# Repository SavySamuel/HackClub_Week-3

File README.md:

# HackClub Week 3: MIDI Keypad

A custom-designed MIDI input device featuring tactile mechanical switches, analog sliders, rotary encoders, and capacitive touch pads.

---

## Overview

This project is a custom MIDI controller built around the waveshare ESP32-S3-ZERO microcontroller. It integrates multiple types of user input: push buttons, sliders, a rotary encoder, and capacitive touch channels which allows for real-time control over music production.

---

## Schematics & Layout

### Schematic
The complete schematic details the wiring for the ESP32-S3-ZERO, rotary encoders (`SW4`), slide potentiometers (`RV1`, `RV2`), mechanical push switches (`SW1`–`SW3`), and capacitive touch headers.

### PCB Layout
The custom 2-layer printed circuit board layout designed in KiCad, routing signals across the front (`F.Cu`) and back (`B.Cu`) copper layers along with some cool art I created a while ago.

### 3D Model
A 3D render preview showcasing the physical layout and placement of components on the hardware.

---

## Features & Hardware Components

- **Microcontroller:** ESP32-S3-ZERO
- **Inputs:**
	- 3x Mechanical Push Switches (`SW1`–`SW3`)
	- 2x Slide Potentiometers / Sliders (`RV1`, `RV2`)
	- 1x Rotary Encoder with Push Switch (`SW4`)
	- Capacitive Touch Button Header (`J1`)

---

> The [Journal](./JOURNAL.md) file details my experience this week

---

## Onshape Case for storing the MIDI Keypad

[Onshape Link](https://cad.onshape.com/documents/9c3e4e1773f598a6c621c8e7/w/239b4c5f4313af9012ed1455/e/c954f826d795d710e863c1da)

> Just a box to store the midi without damaging it. Made it with my MIDI's dimension in sight

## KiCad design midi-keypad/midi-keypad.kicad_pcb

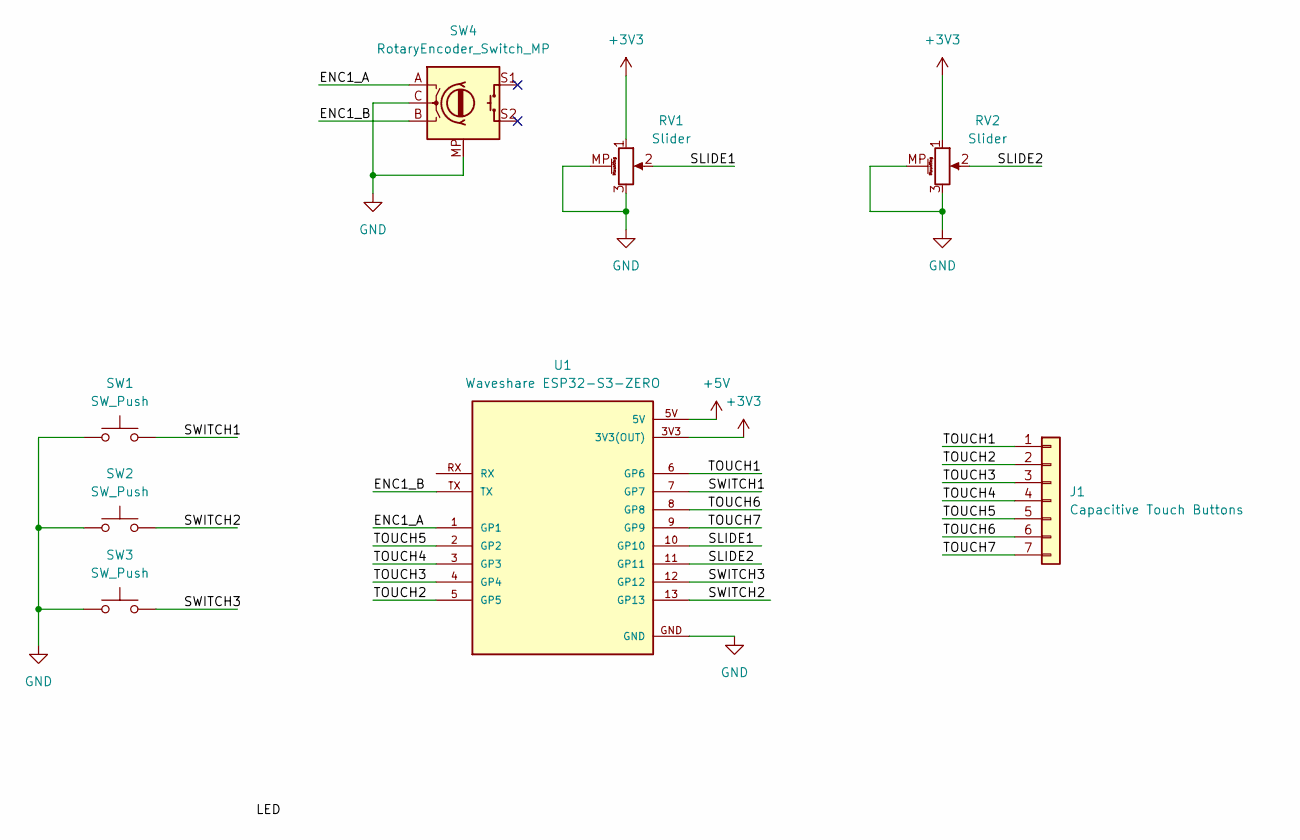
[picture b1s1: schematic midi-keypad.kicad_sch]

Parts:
J1: Capacitive Touch Buttons; Capacitive Keys
RV1, RV2: Slider; Potentiometer_Bourns_PTA1543_Single_Slide
SW1, SW2, SW3: SW_Push; Kailh Choc Low-Profile Switches
SW4: RotaryEncoder_Switch_MP; RotaryEncoder_Alps_EC11E-Switch_Vertical_H20mm
U1: Waveshare ESP32-S3-ZERO; Waveshare ESP32-S3-Zero; PARTREV NA

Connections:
+3V3: RV1.1, RV2.1, U1.3V3 (3V3(OUT))
+5V: U1.5V
/ENC1_A: SW4.A, U1.1 (GP1)
/ENC1_B: SW4.B, U1.TX
/SLIDE1: RV1.2, U1.10 (GP10)
/SLIDE2: RV2.2, U1.11 (GP11)
/SWITCH1: SW1.2, U1.7 (GP7)
/SWITCH2: SW2.2, U1.13 (GP13)
/SWITCH3: SW3.2, U1.12 (GP12)
/TOUCH1: J1.1, U1.6 (GP6)
/TOUCH2: J1.2, U1.5 (GP5)
/TOUCH3: J1.3, U1.4 (GP4)
/TOUCH4: J1.4, U1.3 (GP3)
/TOUCH5: J1.5, U1.2 (GP2)
/TOUCH6: J1.6, U1.8 (GP8)
/TOUCH7: J1.7, U1.9 (GP9)
GND: RV1.3, RV1.MP (MountPin), RV2.3, RV2.MP (MountPin), SW1.1, SW2.1, SW3.1, SW4.C, SW4.MP, U1.GND

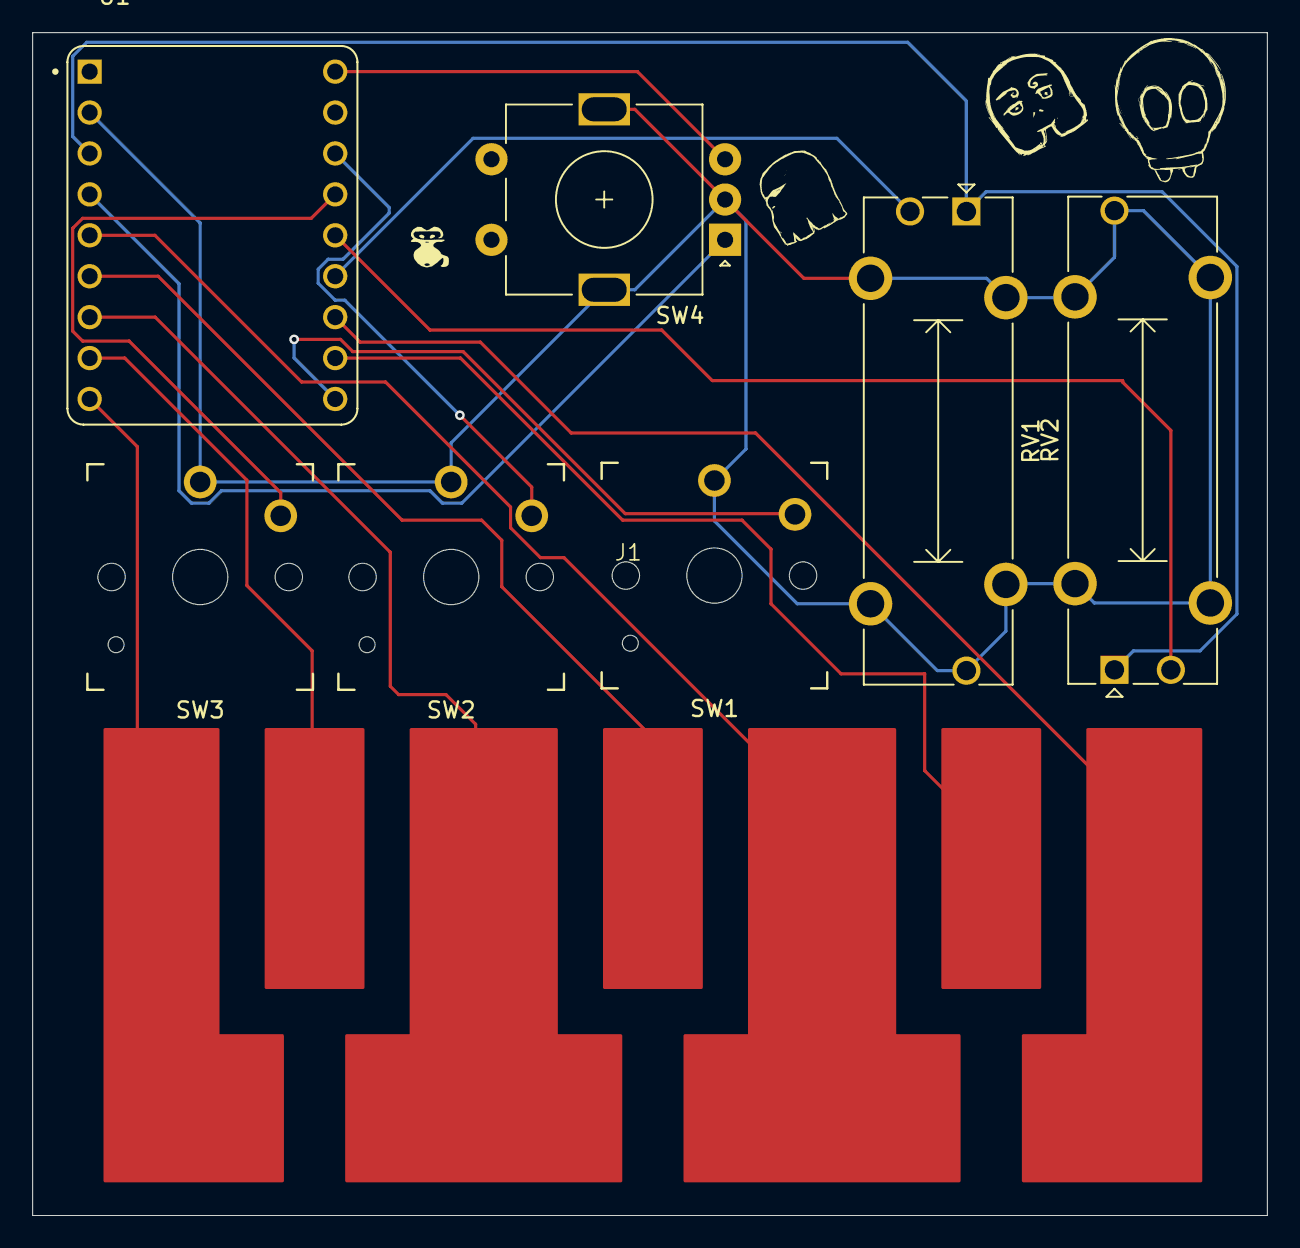
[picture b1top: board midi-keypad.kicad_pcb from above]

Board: 2 copper layers, 76.6 x 73.4 mm, 8 parts (0 on the bottom side), 16 nets.

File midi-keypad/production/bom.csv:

Designator,Footprint,Quantity,Value,LCSC Part #
J1,Capacitive Keys,1,Capacitive Touch Buttons,
"RV1, RV2",Potentiometer_Bourns_PTA1543_Single_Slide,2,Slider,
"SW1, SW2, SW3",Kailh Choc Low-Profile Switches,3,SW_Push,
SW4,RotaryEncoder_Alps_EC11E-Switch_Vertical_H20mm,1,RotaryEncoder_Switch_MP,
U1,Waveshare ESP32-S3-Zero,1,Waveshare ESP32-S3-ZERO,
